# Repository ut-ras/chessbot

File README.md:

# ChessBot: Automated Chessboard

## Overview

ChessBot is an innovative project developed by the IEEE RAS - Demobots team. It is a CNC-inspired automated chessboard designed to enhance the experience of playing chess. Using an actuated electromagnet gantry system, ChessBot can move magnetized chess pieces across the board autonomously, allowing for a seamless game between two players or against a computer-controlled opponent. The project aims to merge the ancient game of chess with modern technology, providing a unique and interactive experience.

## Features

- **Automated Piece Movement**: Moves chess pieces using an electromagnet on a step-driven gantry system, controlled under the board.

- **Magnetized Chess Pieces**: Each piece is magnetized for precise and secure movement. Piece movements are detected via 3D magnetic sensors underneath each square.

- **Player vs. Computer Mode**: Play against an AI with adjustable difficulty settings.

- **Two-Player Online Mode**: Enjoy an enhanced tele-chess experience with automated piece movements that reflect your partner's movements from across the internet using Lichess

## Installation & Setup (WIP)

Make sure you have Python 3.6 or higher installed on your system. You can download it from the [official Python website](https://www.python.org/downloads/).

If on Windows use WSL for now, as the code is not tested on Windows.

1. Clone the repository to your local machine:

```bash
git clone https://github.com/ut-ras/chessbot.git 
```

2. Install the required Python packages:

```bash
cd chessbot
pip install -r requirements.txt
```
3. install stockfish and note what path it is installed to, you will need this for the python script. On Ubuntu or WSL you can do this with the following commands:

```bash
sudo apt-get install stockfish && which stockfish
```
The output of the `which stockfish` command will be the path to the stockfish binary. Copy that path, you will need this for the python script.

4. In the `python/bitboard_with_stockfish.py` file, change the `stockfish_path` variable to the path of the stockfish binary you found in the previous step.

5. Run the Python script:

```bash
python python/bitboard_with_stockfish.py
```

## Software

### Communication Structure

---
### Python Files
- [python/bitboard_with_stockfish.py](python/bitboard_with_stockfish.py) - This is the main file that runs the chess engine. It uses the python-chess library to interface with the Stockfish chess engine. The bitboard implementation is a custom implementation that uses 64-bit integers to represent the chessboard. Makes calls to functions in [python/display_output.py](python/display_output.py), animates the board for a 128x64 display, currently only makes the bitmap.

  - Bitboards are 64bit integer representations of the entire chessboard. 8x8 squares = 64 squares, so a digital for each individual square, that digit is 1 when a piece is on the corresponding square and 0 when a piece is absent from the square.
  - So far we arent using any "standard" bitboard implementations, as our situation is a tad unique. Most chess engines that utilize 12 bitboards, one for each piece type, ( [pawn + knight + bishop + rook + queen + king] * 2 teams = 12 piece types).
  - Here is a diagram of how each space on the chessboard is indexed in the bitboard, the number at each square is the digital that is either high or low depending on if a piece is there or not. For example, square `a4` is position `32`

     ``` 
       8 |  0  1  2  3  4  5  6  7
       7 |  8  9 10 11 12 13 14 15
       6 | 16 17 18 19 20 21 22 23
       5 | 24 25 26 27 28 29 30 31
       4 | 32 33 34 35 36 37 38 39
       3 | 40 41 42 43 44 45 46 47
       2 | 48 49 50 51 52 53 54 55
       1 | 56 57 58 59 60 61 62 63
          -------------------------
          a  b  c  d  e  f  g  h
      ```

## TODO
 - Assemble and test chessboard PCB's - each is an individual rank of the board that connect together.
-  Fill this section in with what we have left to do lol

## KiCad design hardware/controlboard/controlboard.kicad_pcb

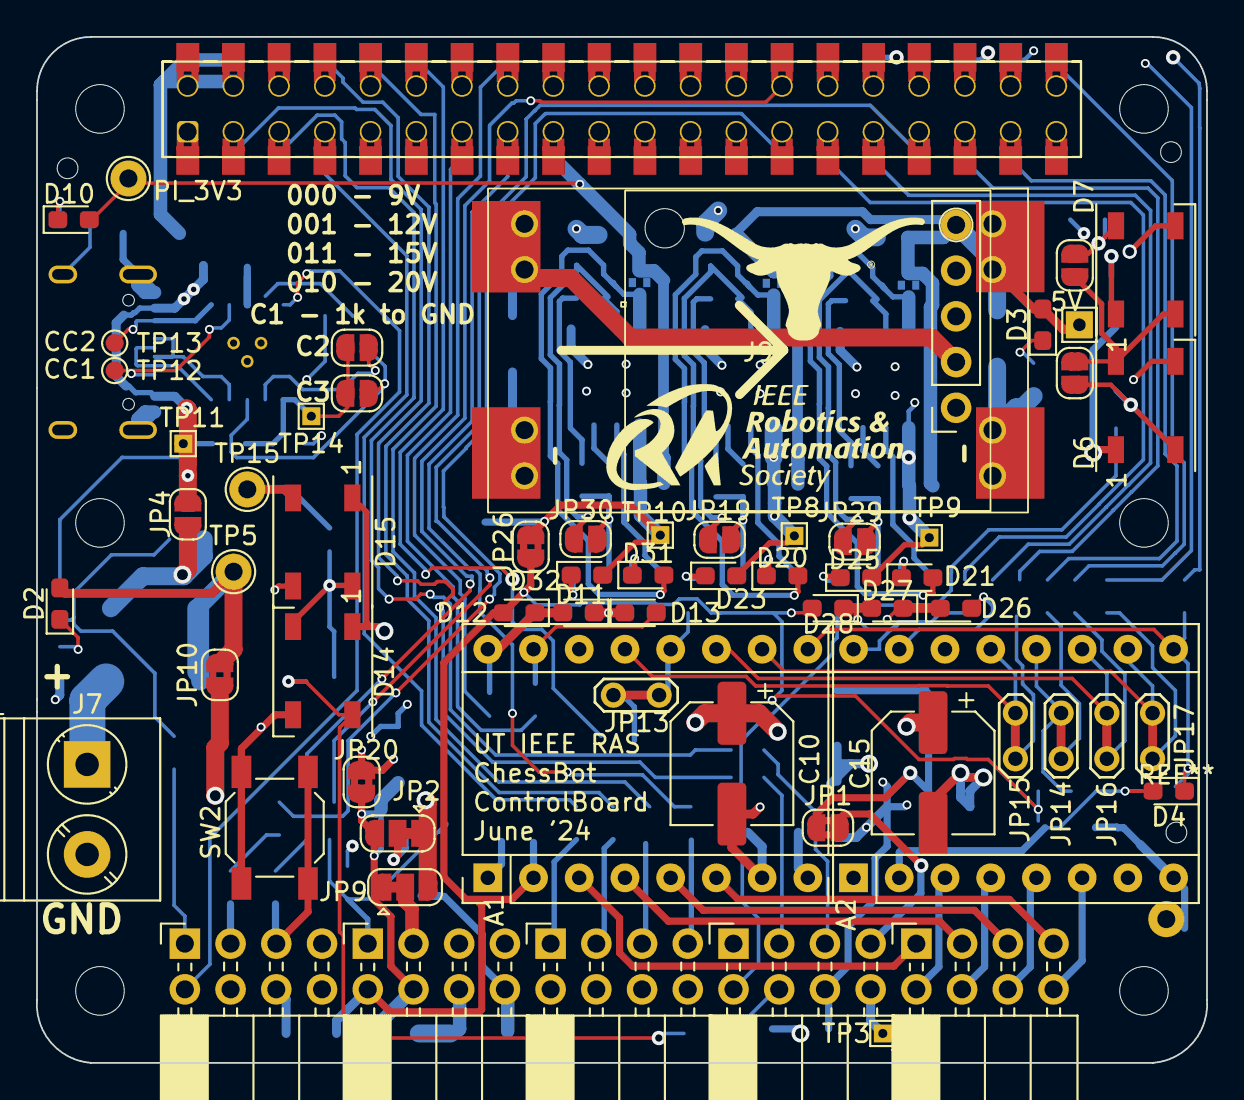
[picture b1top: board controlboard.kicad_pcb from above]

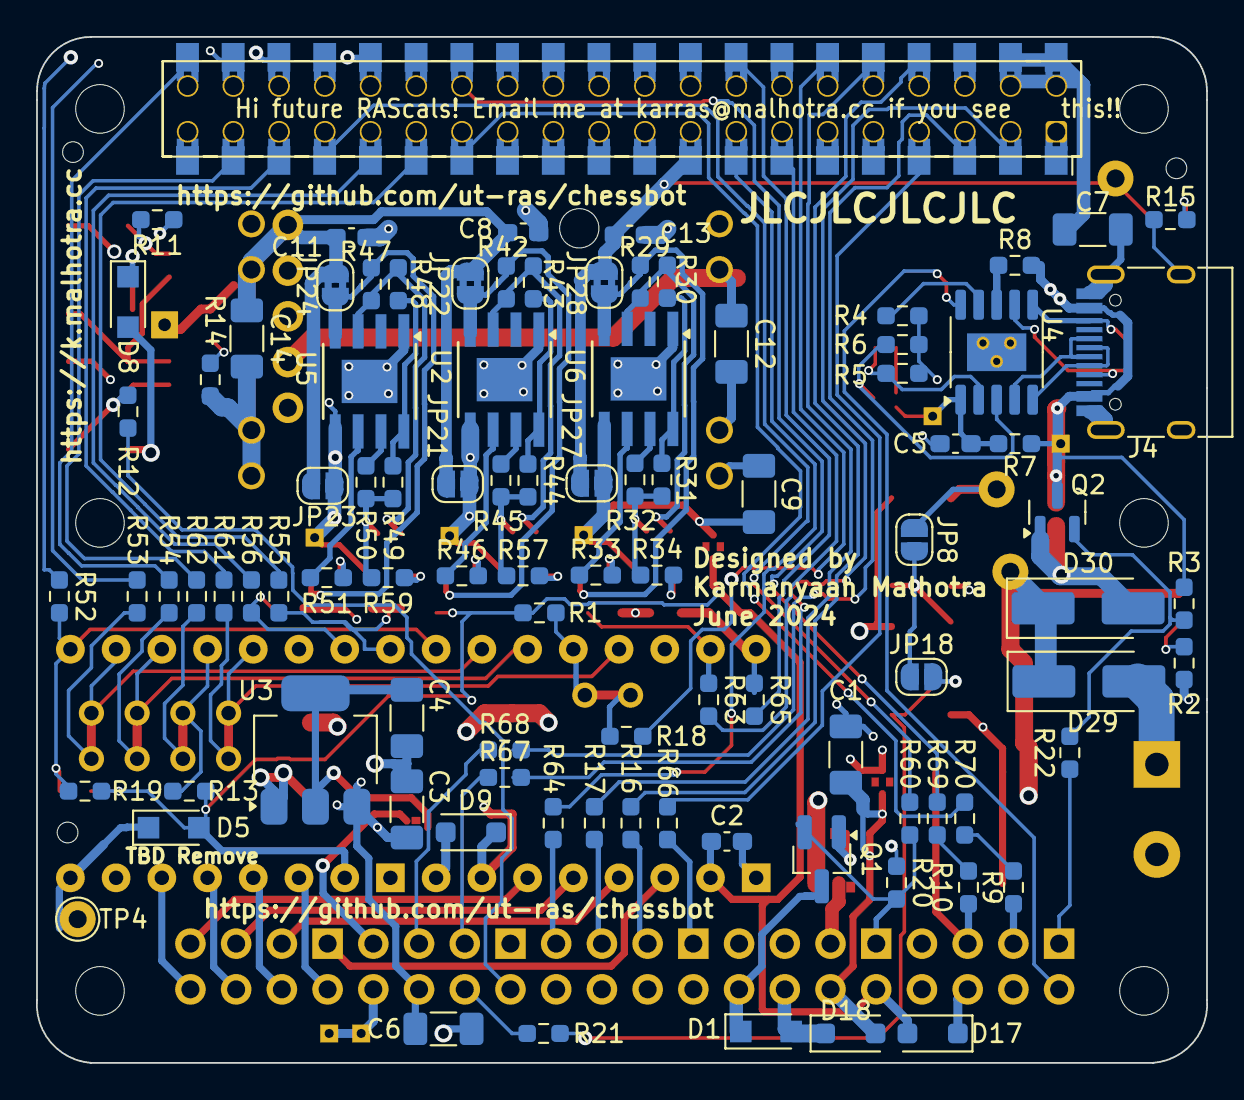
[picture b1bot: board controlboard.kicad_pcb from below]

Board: 4 copper layers, 65.0 x 57.0 mm, 166 parts (95 on the bottom side), 118 nets.

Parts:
A1: Pololu_Breakout_MP6500; Pololu_Breakout-16_15.2x20.3mm
A2: SilentStepStick TMC5160T; Pololu_Breakout-16_15.2x20.3mm
C1, C3, C4, C6, C7, C9, C12, C14: 22uF; C_1206_3216Metric_Pad1.33x1.80mm_HandSolder
C2, C8, C11, C13: 100n; C_0603_1608Metric_Pad1.08x0.95mm_HandSolder
C5: 1u; C_0603_1608Metric_Pad1.08x0.95mm_HandSolder
C10, C15: 100u; CP_Elec_6.3x5.4
D1, D5, D8: SM4007PL; Nexperia_CFP3_SOD-123W
D2, D3, D4, D10: Y; LED_0603_1608Metric_Pad1.05x0.95mm_HandSolder
D6, D7, D14, D15: WS2812B; LED_WS2812B_PLCC4_5.0x5.0mm_P3.2mm
D9: 20V+ D_TVS; D_SOD-123F
D11, D13, D23, D25, D26, D27, D32: G; LED_0603_1608Metric_Pad1.05x0.95mm_HandSolder
D12, D20, D21, D28, D31: R; LED_0603_1608Metric_Pad1.05x0.95mm_HandSolder
D17: 3V3V+ D_TVS; D_SOD-123F
D18: 6V+ D_TVS; D_SOD-123F
D29, D30: SS54; D_SMA_Handsoldering
J1, J3, J6: Conn_02x04_Counter_Clockwise; PinSocket_2x04_P2.54mm_Horizontal
J2: Conn_02x04_Row_Letter_Last; PinSocket_2x04_P2.54mm_Horizontal
J4: TYPE-C-31-M-12; USB_C_Receptacle_HRO_TYPE-C-31-M-12
J5: Conn_02x04_Row_Letter_First; PinSocket_2x04_P2.54mm_Horizontal
J7: Screw_Terminal_01x02; TerminalBlock_Phoenix_PT-1,5-2-5.0-H_1x02_P5.00mm_Horizontal
J9: mini560 voltage regulator; mini560
J11: Pololu Voltage Regulator; reg15d
J27: GPIO; Samtec_HLE-120-02-xxx-DV-BE-A_2x20_P2.54mm_Horizontal
JP1, JP10, JP20, JP22, JP24, JP26, JP28: SolderJumper_2_Bridged; SolderJumper-2_P1.3mm_Bridged2Bar_RoundedPad1.0x1.5mm
JP2, JP9: SolderJumper_3_Bridged12; SolderJumper-3_P1.3mm_Bridged12_RoundedPad1.0x1.5mm
JP4, JP8, JP11, JP12, JP18, JP19, JP29, JP30: SolderJumper_2_Open; SolderJumper-2_P1.3mm_Open_RoundedPad1.0x1.5mm
JP6, JP7: CFG3; SolderJumper-2_P1.3mm_Open_RoundedPad1.0x1.5mm
JP13, JP14, JP15, JP16, JP17: Jumper_2_Bridged; Bridged_TestPoint_2Pads_Pitch2.54mm_Drill0.8mm
JP21, JP23, JP27: Bypass; SolderJumper-2_P1.3mm_Open_RoundedPad1.0x1.5mm
MH1, MH2, MH3, MH3#2, MH4, MH4#2: MountingHole_2.7mm_M2.5
Q1: NMOS AO3400A; SOT-23_Handsoldering
Q2: PMOS AO3401A; SOT-23
R1, R3, R8, R13, R19, R20, R22, R43, R48: 10k; R_0603_1608Metric_Pad0.98x0.95mm_HandSolder
R2, R4, R5, R6, R7, R9, R10, R11, R12, R14, R15, R16, R17, R18, R21, R34, R52, R55, R56, R57, R59, R60, R62, R63, R64, R65, R66: 1k; R_0603_1608Metric_Pad0.98x0.95mm_HandSolder
R29: 82k; R_0603_1608Metric_Pad0.98x0.95mm_HandSolder
R30: 20k; R_0603_1608Metric_Pad0.98x0.95mm_HandSolder
R31, R44, R49: 47k; R_0603_1608Metric_Pad0.98x0.95mm_HandSolder
R32, R33, R46, R51: 3k; R_0603_1608Metric_Pad0.98x0.95mm_HandSolder
R42, R47: 150k; R_0603_1608Metric_Pad0.98x0.95mm_HandSolder
R45, R50: 470R; R_0603_1608Metric_Pad0.98x0.95mm_HandSolder
R53, R54, R61, R67, R68, R69, R70: 100; R_0603_1608Metric_Pad0.98x0.95mm_HandSolder
SW2: SW_Push TODO FP CHECK; SW_SPST_SKQG_WithStem
TP1, TP3, TP8, TP9, TP10, TP11, TP14: TestPoint; TestPoint_THTPad_1.0x1.0mm_Drill0.5mm
TP4, TP5, TP7, TP15: TestPoint; TestPoint_THTPad_D2.0mm_Drill1.0mm
TP6: TestPoint; TestPoint_THTPad_1.5x1.5mm_Drill0.7mm
TP12, TP13: TestPoint; TestPoint_Pad_D1.0mm
U2, U5, U6: TPS25963x; TI_SO-PowerPAD-8
U3: AMS1117-3.3; SOT-223-3_TabPin2
U4: CH224K; SSOP-10-1EP_3.9x4.9mm_P1mm_EP2.1x3.3mm

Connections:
/CH_5V: C3.1, C6.1, C15.1, D6.1 (VDD), D8.2 (A), D14.1 (VDD), D15.1 (VDD), D23.2 (A), J3.6, J6.4, JP20.2 (B), JP21.1 (A), TP8.1, U2.5 (OUT), U3.3 (VI)
/CH_SCL: J3.5, R68.1
/CH_SDA: J3.3, R67.1
/CNC/(CS/I1)1: A1.12 (I1), JP13.2 (B), R1.2
/CNC/(CS/I1)2: A2.12 (CS), JP14.2 (B), R13.2
/CNC/SCK/MS2: A1.11 (MS2), A2.11 (SCK), JP16.2 (B)
/CNC/SDI/MS1: A1.10 (MS1), A2.10 (SDI), JP17.2 (B)
/CNC/SDO/I2: A1.13 (I2), A2.13 (SDO), JP15.2 (B)
/CNC/SERVO_VIN: C1.1, D18.2 (A2), J5.4, JP2.1 (A), JP9.3 (B), JP20.1 (A)
/CNC/VIO: A1.2 (~FLT), A2.2 (VIO), C2.1, D4.2 (A), D5.2 (A), D12.2 (A), D17.2 (A2), D28.2 (A), J5.2, JP26.1 (A), R1.1, R13.1, R19.1
/CNC/VMOT: A1.8 (VMOT), A2.8 (VMOT), C10.1, D5.1 (K), D9.2 (A2), JP2.3 (B), JP9.1 (A), JP10.1 (A), TP4.1
/ChessBoard/3V3: C4.1, JP1.2 (B), U3.2 (VO)
/ChessBoard/LED_IN: D15.2 (DOUT), JP8.1 (A), TP15.1
/ChessBoard/LED_IN_REAL: D14.4 (DIN), JP18.2 (B), R21.2
/ChessBoard/LED_OUT: J3.2, R12.1
/DIR1: A1.16 (DIR), D11.2 (A), D12.1 (K), R65.1
/DIR2: A2.16 (DIR), D27.2 (A), D28.1 (K), R55.1
/ENBL: A1.9 (~ENABLE), A2.9 (~ENABLE), D4.1 (K), R19.2, R52.2
/ID_SCL: J6.5, R10.2, SW2.1
/ID_SDA: J6.3, R9.1
/LED_DATA: D7.4 (DIN), JP11.2 (B), R11.2
/LIM_SW1: J2.1, R66.1
/LIM_SW2: J2.3, R16.2
/LIM_SW3: J2.5, R17.2
/LIM_SW4: J2.7, R64.1
/MAG_PWM: J5.1, Q1.2 (G), R20.2, R60.1
/MOT_CS1: JP13.1 (A), R18.2
/MOT_CS2: JP14.1 (A), R62.1
/MOT_SCK: JP16.1 (A), R54.2
/MOT_SDI: JP17.1 (A), R53.2
/MOT_SDO: JP15.1 (A), R61.1
/PI_3V3: C13.1, D10.2 (A), J27.17, JP27.2 (B), JP28.2 (B), TP7.1
/PI_5V: C7.1, D25.2 (A), J27.2, J27.4, JP23.1 (A), TP9.1, U5.5 (OUT)
/Power/CH_VDD: C5.1, JP6.1 (A), JP7.1 (A), R7.1, TP14.1, U4.1 (VDD)
/Power/CNC_VIO: C9.1, D32.2 (A), JP26.2 (B), JP27.1 (A), TP10.1, U6.5 (OUT)
/Power/PWR_SW_A: J6.2, U4.10 (PG)
/Power/PWR_SW_B: J6.1, R22.1
/Power/UNLIM_5V: C8.1, C11.1, C14.1, D3.2 (A), J9.1, J11.5, JP21.2 (B), JP22.2 (B), JP23.2 (B), JP24.2 (B), TP6.1
/Power/UNLIM_VIN: C12.1, D2.2 (A), D29.1 (K), D30.1 (K), J6.8, J9.3, J11.2, JP10.2 (B), TP5.1
/Power/VBUS: J4.A4 (VBUS), J4.A9 (VBUS), J4.B4 (VBUS), J4.B9 (VBUS), JP4.1 (A), Q2.3 (S), R3.1, R7.2, R8.2, TP11.1
/STEP1: A1.15 (STEP), D13.2 (A), R63.1
/STEP2: A2.15 (STEP), D26.2 (A), R56.1
GND: A1.1 (GND), A1.7 (GND), A2.1 (GND), A2.7 (GND), C1.2, C2.2, C3.2, C4.2, C5.2, C6.2, C7.2, C8.2, C9.2, C10.2, C11.2, C12.2, C13.2, C14.2, C15.2, D1.2 (A), D6.3 (VSS), D7.3 (VSS), D9.1 (A1), D11.1 (K), D13.1 (K), D14.3 (VSS), D15.3 (VSS), D17.1 (A1), D18.1 (A1), D26.1 (K), D27.1 (K), J2.2, J2.4, J2.6, J2.8, J3.1, J4.A1 (GND), J4.A12 (GND), J4.B1 (GND), J4.B12 (GND), J4.S1 (SHIELD), J5.5, J5.6, J5.7, J6.6, J6.7, J7.2, J9.2, J9.4, J11.3, J11.4, J27.6, J27.9, J27.14, J27.20, J27.25, J27.30, J27.34, J27.39, JP19.1 (A), JP29.1 (A), JP30.1 (A), R2.1, R4.1, R5.1, R6.1, R14.1, R15.1, R20.1, R31.2, R32.2, R34.1, R44.2, R45.2, R49.2, R50.2, R57.1, R59.1, SW2.2, U2.1 (GND), U2.9 (GND), U3.1 (GND), U4.11 (GND), U5.1 (GND), U5.9 (GND), U6.1 (GND), U6.9 (GND)
unnamed: A1.4 (1A), J1.3
unnamed: A1.3 (1B), J1.1
unnamed: A1.5 (2A), J1.5
unnamed: A1.6 (2B), J1.7
unnamed: A2.4 (1A), J1.4
unnamed: A2.3 (1B), J1.2
unnamed: A2.5 (2A), J1.6
unnamed: A2.6 (2B), J1.8
unnamed: D1.1 (K), J5.8, Q1.3 (S)
unnamed: D2.1 (K), R2.2
unnamed: D3.1 (K), R14.2
unnamed: D6.4 (DIN), D7.2 (DOUT), JP11.1 (A), JP12.2 (B)
unnamed: D6.2 (DOUT), JP12.1 (A), R12.2
unnamed: D7.1 (VDD), D8.1 (K)
unnamed: D10.1 (K), R15.2
unnamed: D14.2 (DOUT), D15.4 (DIN), JP8.2 (B), JP18.1 (A)
unnamed: D20.2 (A), JP22.1 (A), R42.1, U2.4 (IN)
unnamed: D20.1 (K), R46.2
unnamed: D21.2 (A), JP24.1 (A), R47.1, U5.4 (IN)
unnamed: D21.1 (K), R51.2
unnamed: D23.1 (K), R57.2
unnamed: D25.1 (K), R59.2
unnamed: D29.2 (A), J7.1
unnamed: D30.2 (A), JP4.2 (B), Q2.1 (D)
unnamed: D31.2 (A), JP28.1 (A), R29.1, U6.4 (IN)
unnamed: D31.1 (K), R33.2
unnamed: D32.1 (K), R34.2
unnamed: J3.4, R21.1
unnamed: J3.7, JP1.1 (A)
unnamed: J3.8, TP1.1, TP3.1
unnamed: J4.A5 (CC1), TP12.1, U4.7 (CC1)
unnamed: J4.B5 (CC2), TP13.1, U4.6 (CC2)
unnamed: J5.3, JP2.2 (C)
unnamed: J27.3, R67.2
unnamed: J27.5, R68.2
unnamed: J27.7, R66.2
unnamed: J27.8, R16.1
unnamed: J27.10, R17.1
unnamed: J27.12, R18.1
unnamed: J27.13, R63.2
unnamed: J27.15, R64.2
unnamed: J27.16, R65.2
unnamed: J27.27, R70.2
unnamed: J27.28, R69.1
unnamed: J27.29, R55.2
unnamed: J27.31, R56.2
unnamed: J27.32, R11.1
unnamed: J27.33, R60.2
unnamed: J27.35, R61.2
unnamed: J27.36, R52.1
unnamed: J27.37, R62.2
unnamed: J27.38, R53.1
unnamed: J27.40, R54.1
unnamed: JP6.2 (B), R5.2, U4.2 (CFG2)
unnamed: JP7.2 (B), R6.2, U4.3 (CFG3)
unnamed: JP9.2 (C), Q1.1 (D)
unnamed: JP19.2 (B), R42.2, R43.1, U2.3 (EN/UVLO)
unnamed: JP29.2 (B), R47.2, R48.1, U5.3 (EN/UVLO)
unnamed: JP30.2 (B), R29.2, R30.1, U6.3 (EN/UVLO)
unnamed: Q2.2 (G), R3.2, R22.2
unnamed: R10.1, R69.2
unnamed: R9.2, R70.1
unnamed: R45.1, U2.7 (ILim)
unnamed: R43.2, R44.1, U2.8 (OVLO)
unnamed: R46.1, U2.6 (~FLT)
unnamed: R4.2, U4.9 (CFG1)
unnamed: J4.A7 (D-), J4.B7 (D-), U4.5 (DM)
unnamed: J4.A6 (D+), J4.B6 (D+), U4.4 (DP)
unnamed: R8.1, U4.8 (VBUS)
unnamed: R50.1, U5.7 (ILim)
unnamed: R48.2, R49.1, U5.8 (OVLO)
unnamed: R51.1, U5.6 (~FLT)
unnamed: R32.1, U6.7 (ILim)
unnamed: R30.2, R31.1, U6.8 (OVLO)
unnamed: R33.1, U6.6 (~FLT)

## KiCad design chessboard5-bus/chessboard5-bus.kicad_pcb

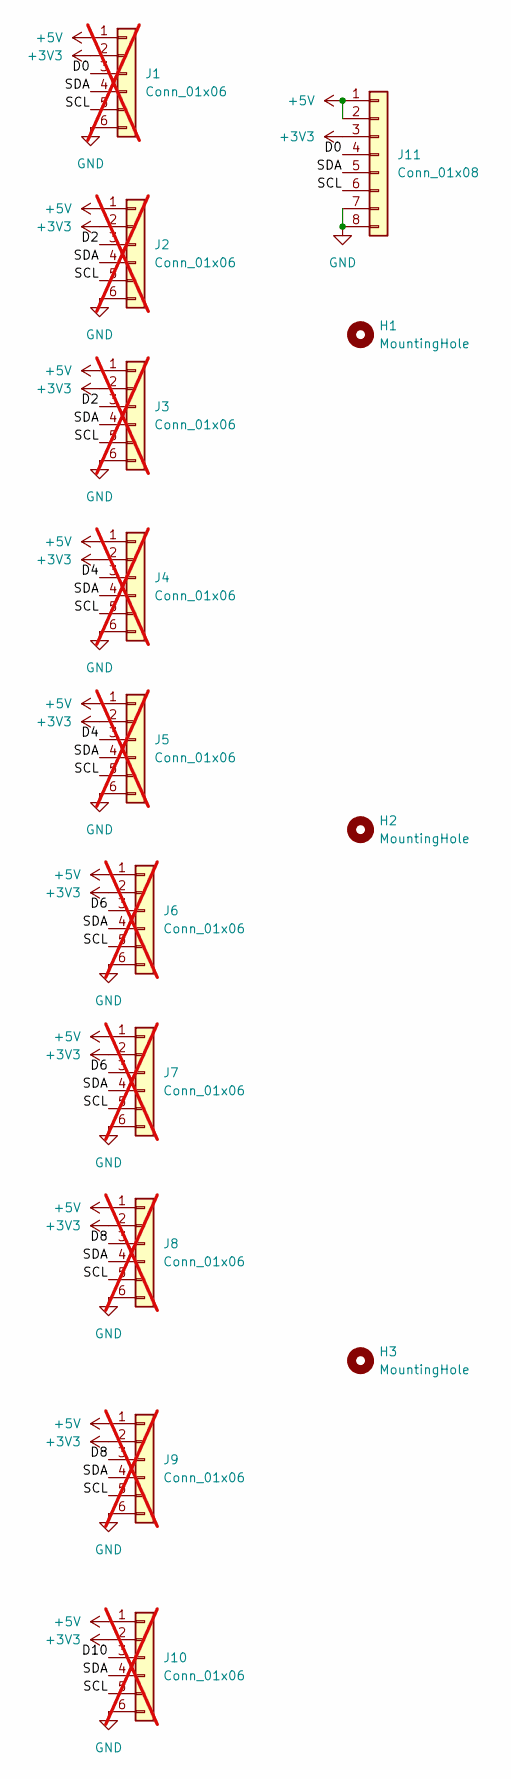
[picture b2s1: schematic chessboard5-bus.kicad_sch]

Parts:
H1, H2, H3: MountingHole; MountingHole_3.2mm_M3
J1, J2, J3, J4, J5, J6, J7, J8, J9, J10: Conn_01x06; PinHeader_2x03_P2.54mm_Vertical; not fitted
J11: Conn_01x08; JST_PH_S8B-PH-SM4-TB_1x08-1MP_P2.00mm_Horizontal

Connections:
+3V3: J1.2, J2.2, J3.2, J4.2, J5.2, J6.2, J7.2, J8.2, J9.2, J10.2, J11.3
+5V: J1.1, J2.1, J3.1, J4.1, J5.1, J6.1, J7.1, J8.1, J9.1, J10.1, J11.1, J11.2
/D0: J1.3, J11.4
/D2: J2.3, J3.3
/D4: J4.3, J5.3
/D6: J6.3, J7.3
/D8: J8.3, J9.3
/D10: J10.3
/SCL: J1.5, J2.5, J3.5, J4.5, J5.5, J6.5, J7.5, J8.5, J9.5, J10.5, J11.6
/SDA: J1.4, J2.4, J3.4, J4.4, J5.4, J6.4, J7.4, J8.4, J9.4, J10.4, J11.5
GND: J1.6, J2.6, J3.6, J4.6, J5.6, J6.6, J7.6, J8.6, J9.6, J10.6, J11.7, J11.8

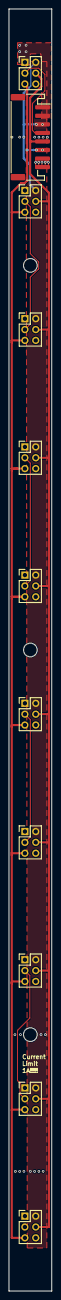
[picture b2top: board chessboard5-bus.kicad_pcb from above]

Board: 2 copper layers, 10.0 x 300.0 mm, 14 parts (0 on the bottom side), 10 nets.

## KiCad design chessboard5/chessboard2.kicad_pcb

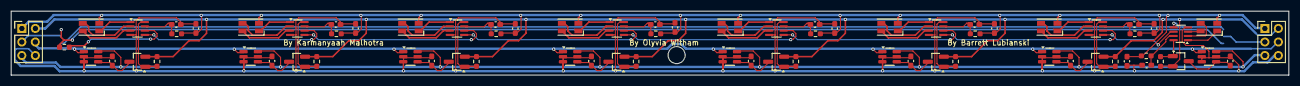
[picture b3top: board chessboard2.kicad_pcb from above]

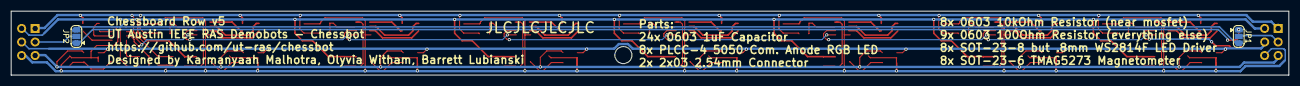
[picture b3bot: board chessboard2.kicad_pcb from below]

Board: 2 copper layers, 240.0 x 12.0 mm, 78 parts (2 on the bottom side), 65 nets.

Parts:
C1, C2, C3, C4, C5, C6, C7, C8, C9, C10, C11, C12, C13, C14, C15, C16, C17, C18, C19, C20, C21, C22, C23, C24: 1u; C_0603_1608Metric_Pad1.08x0.95mm_HandSolder
D9, D10, D11, D12, D13, D14, D15, D16: LED_RGAB; LED_RGB_Wuerth-PLCC4_3.2x2.8mm_150141M173100
H1: MountingHole; MountingHole_3.2mm_M3
J1, J2: Conn_01x06; PinHeader_2x03_P2.54mm_Vertical
JP1, JP2: SolderJumper_3_Open; SolderJumper-3_P1.3mm_Open_RoundedPad1.0x1.5mm
Q1, Q2, Q3, Q4, Q5, Q6, Q7, Q8: AO3401A; SOT-23_Handsoldering
R1, R3, R5, R7, R9, R11, R13, R15, R17: 100R; R_0603_1608Metric_Pad0.98x0.95mm_HandSolder
R2, R4, R6, R8, R10, R12, R14, R16: 10k; R_0603_1608Metric_Pad0.98x0.95mm_HandSolder
U1, U3, U5, U7, U9, U11, U13, U15: WS2814F; FSOP-8
U2, U4, U6, U8, U10, U12, U14, U16: TMAG5273; SOT-23-6_Handsoldering

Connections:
+3.3V: J1.2, J2.2, Q1.2 (S), Q2.2 (S), Q3.2 (S), Q4.2 (S), Q5.2 (S), Q6.2 (S), Q7.2 (S), Q8.2 (S), R2.2, R4.2, R6.2, R8.2, R10.2, R12.2, R14.2, R16.2
+5V: C1.1, C4.1, C7.1, C10.1, C13.1, C16.1, C19.1, C22.1, D9.4 (A), D10.4 (A), D11.4 (A), D12.4 (A), D13.4 (A), D14.4 (A), D15.4 (A), D16.4 (A), J1.1, J2.1, R1.1, R3.1, R5.1, R7.1, R9.1, R11.1, R13.1, R15.1
/Cell1/DOUT: U3.5 (DO), U5.6 (DIN)
/Cell2/DOUT: U5.5 (DO), U7.6 (DIN)
/Cell3/DOUT: U7.5 (DO), U9.6 (DIN)
/Cell4/DOUT: U9.5 (DO), U11.6 (DIN)
/Cell5/DOUT: U11.5 (DO), U13.6 (DIN)
/Cell6/DOUT: U13.5 (DO), U15.6 (DIN)
/Cell/DIN: R17.1, U1.6 (DIN)
/Cell/DOUT: U1.5 (DO), U3.6 (DIN)
/DIN_G: JP1.1 (A), JP2.1 (A), R17.2
/DOUT_G: JP1.3 (B), JP2.3 (B), U15.5 (DO)
GND: C1.2, C2.2, C3.2, C4.2, C5.2, C6.2, C7.2, C8.2, C9.2, C10.2, C11.2, C12.2, C13.2, C14.2, C15.2, C16.2, C17.2, C18.2, C19.2, C20.2, C21.2, C22.2, C23.2, C24.2, J1.6, J2.6, U1.4 (GND), U2.2 (GND), U2.3 (GND), U2.5 (GND), U3.4 (GND), U4.2 (GND), U4.3 (GND), U4.5 (GND), U5.4 (GND), U6.2 (GND), U6.3 (GND), U6.5 (GND), U7.4 (GND), U8.2 (GND), U8.3 (GND), U8.5 (GND), U9.4 (GND), U10.2 (GND), U10.3 (GND), U10.5 (GND), U11.4 (GND), U12.2 (GND), U12.3 (GND), U12.5 (GND), U13.4 (GND), U14.2 (GND), U14.3 (GND), U14.5 (GND), U15.4 (GND), U16.2 (GND), U16.3 (GND), U16.5 (GND)
unnamed: D9.2 (BK), U1.2 (OUTG)
unnamed: D9.1 (GK), U1.3 (OUTB)
unnamed: D9.3 (RK), U1.1 (OUTR)
unnamed: D10.2 (BK), U3.2 (OUTG)
unnamed: D10.1 (GK), U3.3 (OUTB)
unnamed: D10.3 (RK), U3.1 (OUTR)
unnamed: D11.2 (BK), U5.2 (OUTG)
unnamed: D11.1 (GK), U5.3 (OUTB)
unnamed: D11.3 (RK), U5.1 (OUTR)
unnamed: D12.2 (BK), U7.2 (OUTG)
unnamed: D12.1 (GK), U7.3 (OUTB)
unnamed: D12.3 (RK), U7.1 (OUTR)
unnamed: D13.2 (BK), U9.2 (OUTG)
unnamed: D13.1 (GK), U9.3 (OUTB)
unnamed: D13.3 (RK), U9.1 (OUTR)
unnamed: D14.2 (BK), U11.2 (OUTG)
unnamed: D14.1 (GK), U11.3 (OUTB)
unnamed: D14.3 (RK), U11.1 (OUTR)
unnamed: D15.2 (BK), U13.2 (OUTG)
unnamed: D15.1 (GK), U13.3 (OUTB)
unnamed: D15.3 (RK), U13.1 (OUTR)
unnamed: D16.2 (BK), U15.2 (OUTG)
unnamed: D16.1 (GK), U15.3 (OUTB)
unnamed: D16.3 (RK), U15.1 (OUTR)
unnamed: J1.3, JP2.2 (C)
unnamed: J2.3, JP1.2 (C)
unnamed: C3.1, Q1.3 (D), U2.4 (VDD)
unnamed: Q1.1 (G), R2.1, U1.8 (OUTW)
unnamed: C6.1, Q2.3 (D), U4.4 (VDD)
unnamed: Q2.1 (G), R4.1, U3.8 (OUTW)
unnamed: C9.1, Q3.3 (D), U6.4 (VDD)
unnamed: Q3.1 (G), R6.1, U5.8 (OUTW)
unnamed: C12.1, Q4.3 (D), U8.4 (VDD)
unnamed: Q4.1 (G), R8.1, U7.8 (OUTW)
unnamed: C15.1, Q5.3 (D), U10.4 (VDD)
unnamed: Q5.1 (G), R10.1, U9.8 (OUTW)
unnamed: C18.1, Q6.3 (D), U12.4 (VDD)
unnamed: Q6.1 (G), R12.1, U11.8 (OUTW)
unnamed: C21.1, Q7.3 (D), U14.4 (VDD)
unnamed: Q7.1 (G), R14.1, U13.8 (OUTW)
unnamed: C24.1, Q8.3 (D), U16.4 (VDD)
unnamed: Q8.1 (G), R16.1, U15.8 (OUTW)
unnamed: C2.1, R1.2, U1.7 (VDD)
unnamed: C5.1, R3.2, U3.7 (VDD)
unnamed: C8.1, R5.2, U5.7 (VDD)
unnamed: C11.1, R7.2, U7.7 (VDD)
unnamed: C14.1, R9.2, U9.7 (VDD)
unnamed: C17.1, R11.2, U11.7 (VDD)
unnamed: C20.1, R13.2, U13.7 (VDD)
unnamed: C23.1, R15.2, U15.7 (VDD)
SCL: J1.5, J2.5, U2.6 (SDA/ADDR), U4.6 (SDA/ADDR), U6.6 (SDA/ADDR), U8.6 (SDA/ADDR), U10.6 (SDA/ADDR), U12.6 (SDA/ADDR), U14.6 (SDA/ADDR), U16.6 (SDA/ADDR)
SDA: J1.4, J2.4, U2.1 (SCL/INT), U4.1 (SCL/INT), U6.1 (SCL/INT), U8.1 (SCL/INT), U10.1 (SCL/INT), U12.1 (SCL/INT), U14.1 (SCL/INT), U16.1 (SCL/INT)

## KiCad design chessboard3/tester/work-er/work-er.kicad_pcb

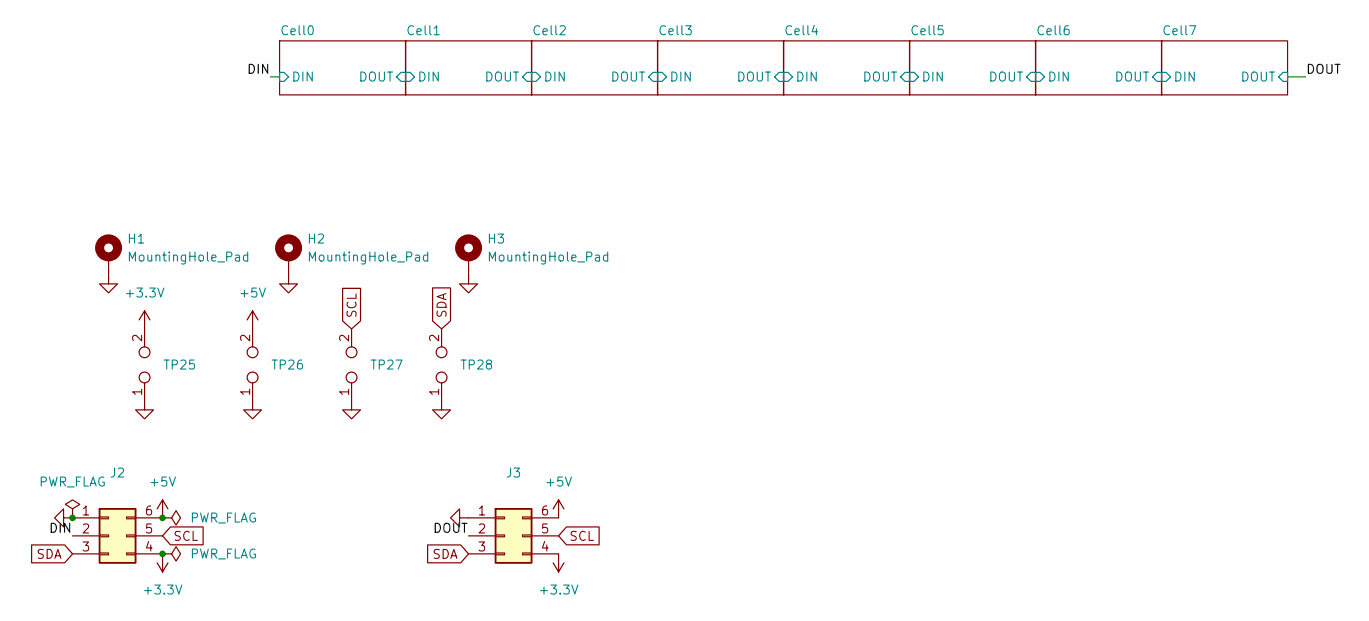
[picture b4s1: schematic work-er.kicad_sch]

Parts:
H1, H2, H3: MountingHole_Pad; MountingHole_2.2mm_M2_DIN965_Pad
J2, J3: Conn_02x03_Counter_Clockwise; PinHeader_2x03_P2.54mm_Vertical
TP25, TP26, TP27, TP28: TestPoint_2Pole; TestPoint_2Pads_Pitch2.54mm_Drill0.8mm

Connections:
+3.3V: J2.4, J3.4, TP25.2; also elsewhere on the board
+5V: J2.6, J3.6, TP26.2; also elsewhere on the board
/DIN: J2.2; also elsewhere on the board
/DOUT: J3.2; also elsewhere on the board
GND: H1.1, H2.1, H3.1, J2.1, J3.1, TP25.1, TP26.1, TP27.1, TP28.1; also elsewhere on the board
SCL: J2.5, J3.5, TP27.2; also elsewhere on the board
SDA: J2.3, J3.3, TP28.2; also elsewhere on the board

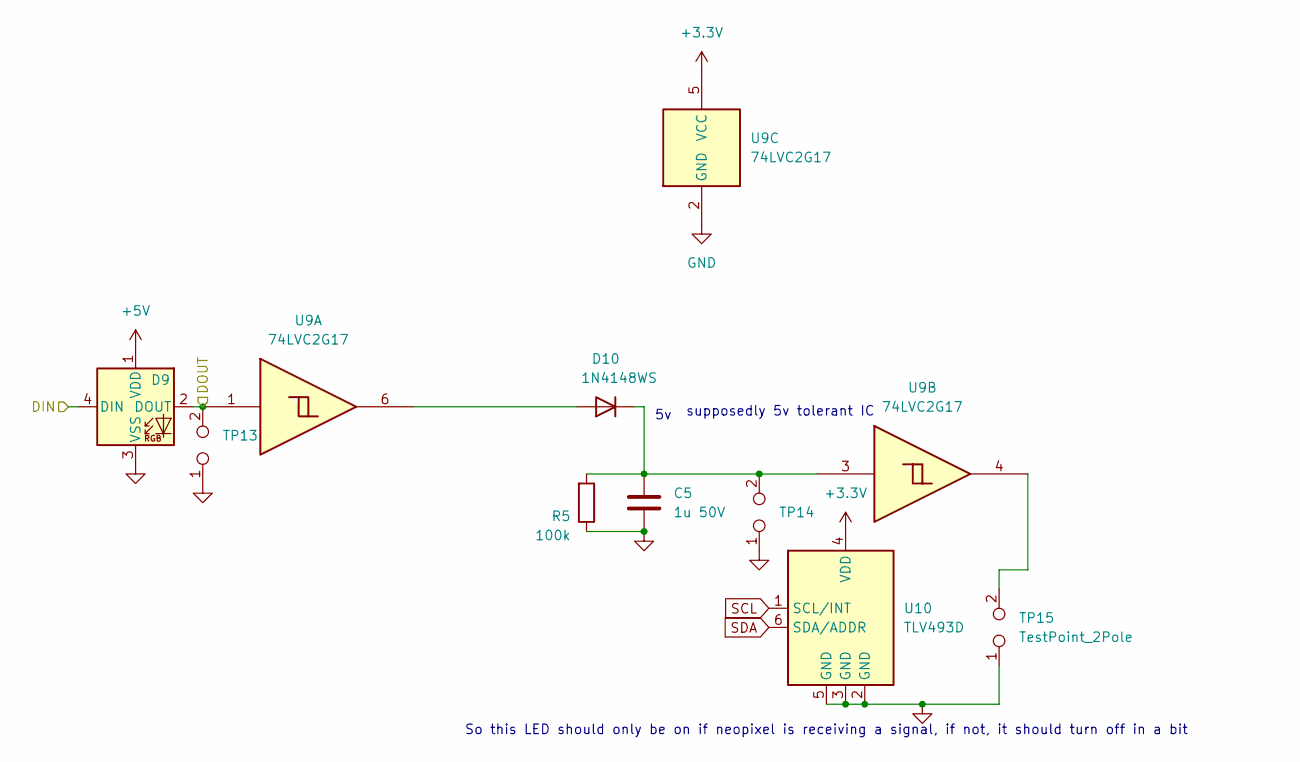
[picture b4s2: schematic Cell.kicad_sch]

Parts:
C5: 1u 50V; C_0603_1608Metric
D9: sk6812-mini-e; SK6812-MINI-E
D10: 1N4148WS; D_SOD-323_HandSoldering
R5: 100k; R_0603_1608Metric_Pad0.98x0.95mm_HandSolder
TP13, TP14, TP15: TestPoint_2Pole; TestPoint_2Pads_Pitch2.54mm_Drill0.8mm
U9: 74LVC2G17; SOT-363_SC-70-6_Handsoldering
U10: TLV493D; SOT-23-6_Handsoldering

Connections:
+3.3V: U9.5 (VCC), U10.4 (VDD); also elsewhere on the board
+5V: D9.1 (VDD); also elsewhere on the board
/Cell3/DOUT: D9.4 (DIN); also elsewhere on the board
/Cell4/DOUT: D9.2 (DOUT), TP13.2, U9.1; also elsewhere on the board
GND: C5.2, D9.3 (VSS), R5.1, TP13.1, TP14.1, TP15.1, U9.2 (GND), U10.2 (GND), U10.3 (GND), U10.5 (GND); also elsewhere on the board
unnamed: D10.2 (A), U9.6
unnamed: C5.1, D10.1 (K), R5.2, TP14.2, U9.3
unnamed: TP15.2, U9.4
SCL: U10.1 (SCL/INT); also elsewhere on the board
SDA: U10.6 (SDA/ADDR); also elsewhere on the board

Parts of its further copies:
C1, C2, C3, C4, C6, C7, C8: 1u 50V; C_0603_1608Metric
D1, D3, D5, D7, D11, D13, D15: sk6812-mini-e; SK6812-MINI-E
D2, D4, D6, D8, D12, D14, D16: 1N4148WS; D_SOD-323_HandSoldering
R1, R2, R3, R4, R6, R7, R8: 100k; R_0603_1608Metric_Pad0.98x0.95mm_HandSolder
TP1, TP2, TP3, TP4, TP5, TP6, TP7, TP8, TP9, TP10, TP11, TP12, TP16, TP17, TP18, TP19, TP20, TP21, TP22, TP23, TP24: TestPoint_2Pole; TestPoint_2Pads_Pitch2.54mm_Drill0.8mm
U1, U3, U5, U7, U11, U13, U15: 74LVC2G17; SOT-363_SC-70-6_Handsoldering
U2, U4, U6, U8, U12, U14, U16: TLV493D; SOT-23-6_Handsoldering

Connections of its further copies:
+3.3V: U1.5 (VCC), U2.4 (VDD), U3.5 (VCC), U4.4 (VDD), U5.5 (VCC), U6.4 (VDD), U7.5 (VCC), U8.4 (VDD), U11.5 (VCC), U12.4 (VDD), U13.5 (VCC), U14.4 (VDD), U15.5 (VCC), U16.4 (VDD); also elsewhere on the board
+5V: D1.1 (VDD), D3.1 (VDD), D5.1 (VDD), D7.1 (VDD), D11.1 (VDD), D13.1 (VDD), D15.1 (VDD); also elsewhere on the board
/Cell0/DOUT: D1.2 (DOUT), D3.4 (DIN), TP1.2, U1.1
/Cell1/DOUT: D3.2 (DOUT), D5.4 (DIN), TP4.2, U3.1
/Cell2/DOUT: D5.2 (DOUT), D7.4 (DIN), TP7.2, U5.1
/Cell3/DOUT: D7.2 (DOUT), TP10.2, U7.1; also elsewhere on the board
/Cell4/DOUT: D11.4 (DIN); also elsewhere on the board
/Cell5/DOUT: D11.2 (DOUT), D13.4 (DIN), TP16.2, U11.1
/Cell6/DOUT: D13.2 (DOUT), D15.4 (DIN), TP19.2, U13.1
/DIN: D1.4 (DIN); also elsewhere on the board
/DOUT: D15.2 (DOUT), TP22.2, U15.1; also elsewhere on the board
GND: C1.2, C2.2, C3.2, C4.2, C6.2, C7.2, C8.2, D1.3 (VSS), D3.3 (VSS), D5.3 (VSS), D7.3 (VSS), D11.3 (VSS), D13.3 (VSS), D15.3 (VSS), R1.1, R2.1, R3.1, R4.1, R6.1, R7.1, R8.1, TP1.1, TP2.1, TP3.1, TP4.1, TP5.1, TP6.1, TP7.1, TP8.1, TP9.1, TP10.1, TP11.1, TP12.1, TP16.1, TP17.1, TP18.1, TP19.1, TP20.1, TP21.1, TP22.1, TP23.1, TP24.1, U1.2 (GND), U2.2 (GND), U2.3 (GND), U2.5 (GND), U3.2 (GND), U4.2 (GND), U4.3 (GND), U4.5 (GND), U5.2 (GND), U6.2 (GND), U6.3 (GND), U6.5 (GND), U7.2 (GND), U8.2 (GND), U8.3 (GND), U8.5 (GND), U11.2 (GND), U12.2 (GND), U12.3 (GND), U12.5 (GND), U13.2 (GND), U14.2 (GND), U14.3 (GND), U14.5 (GND), U15.2 (GND), U16.2 (GND), U16.3 (GND), U16.5 (GND); also elsewhere on the board
unnamed: D2.2 (A), U1.6
unnamed: C1.1, D2.1 (K), R1.2, TP2.2, U1.3
unnamed: D4.2 (A), U3.6
unnamed: C2.1, D4.1 (K), R2.2, TP5.2, U3.3
unnamed: D6.2 (A), U5.6
unnamed: C3.1, D6.1 (K), R3.2, TP8.2, U5.3
unnamed: D8.2 (A), U7.6
unnamed: C4.1, D8.1 (K), R4.2, TP11.2, U7.3
unnamed: D12.2 (A), U11.6
unnamed: C6.1, D12.1 (K), R6.2, TP17.2, U11.3
unnamed: D14.2 (A), U13.6
unnamed: C7.1, D14.1 (K), R7.2, TP20.2, U13.3
unnamed: D16.2 (A), U15.6
unnamed: C8.1, D16.1 (K), R8.2, TP23.2, U15.3
unnamed: TP3.2, U1.4
unnamed: TP6.2, U3.4
unnamed: TP9.2, U5.4
unnamed: TP12.2, U7.4
unnamed: TP18.2, U11.4
unnamed: TP21.2, U13.4
unnamed: TP24.2, U15.4
SCL: U2.1 (SCL/INT), U4.1 (SCL/INT), U6.1 (SCL/INT), U8.1 (SCL/INT), U12.1 (SCL/INT), U14.1 (SCL/INT), U16.1 (SCL/INT); also elsewhere on the board
SDA: U2.6 (SDA/ADDR), U4.6 (SDA/ADDR), U6.6 (SDA/ADDR), U8.6 (SDA/ADDR), U12.6 (SDA/ADDR), U14.6 (SDA/ADDR), U16.6 (SDA/ADDR); also elsewhere on the board

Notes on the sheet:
supposedly 5v tolerant IC
So this LED should only be on if neopixel is receiving a signal, if not, it should turn off in a bit

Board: 2 copper layers, 81 parts (0 on the bottom side), 38 nets, no tracks yet.

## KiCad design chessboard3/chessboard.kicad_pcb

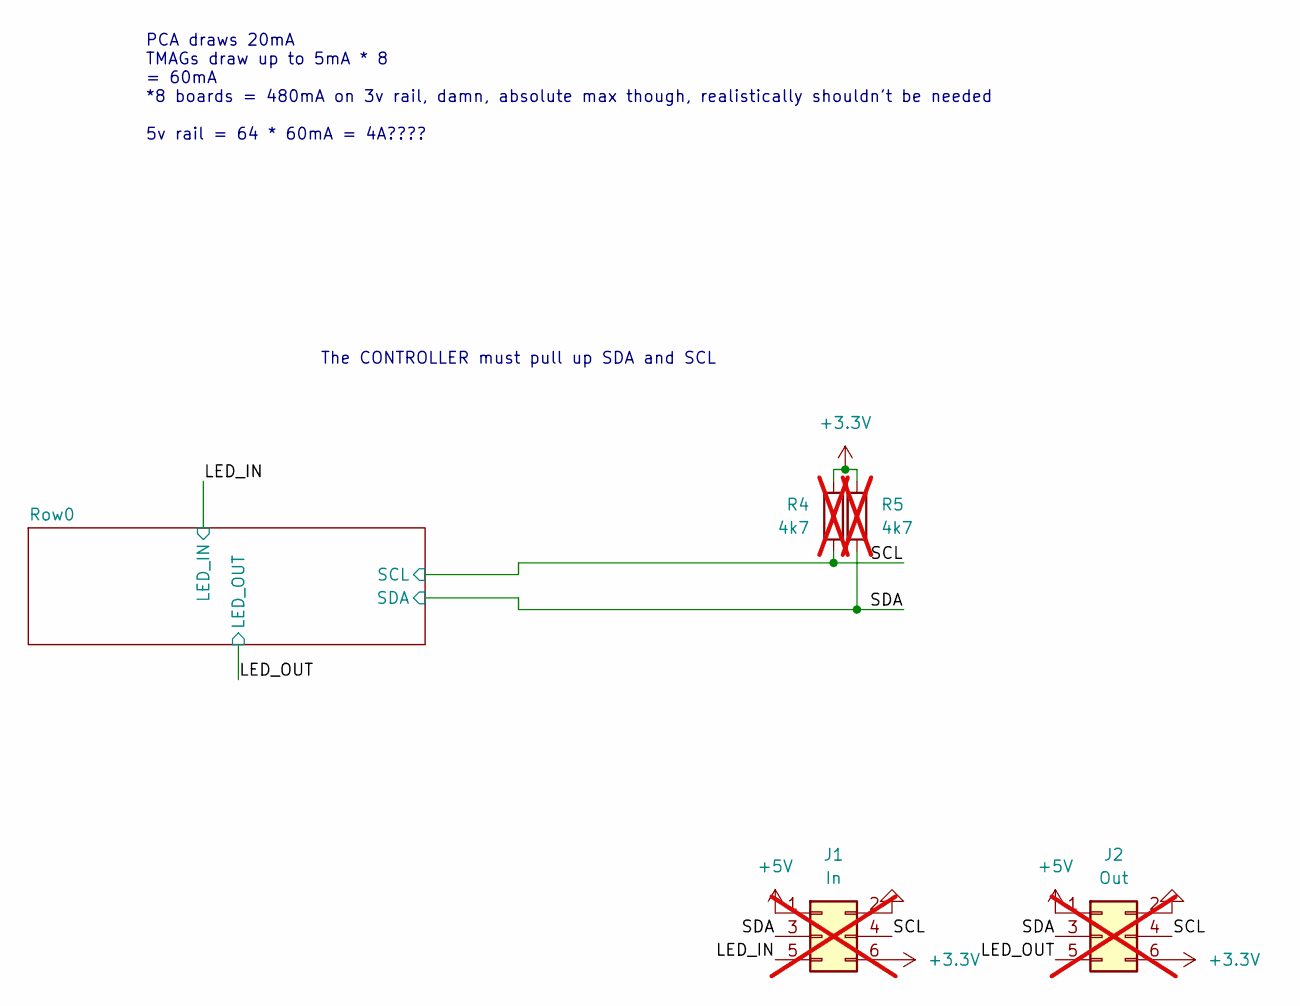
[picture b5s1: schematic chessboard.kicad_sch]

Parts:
J1: In; PinSocket_2x03_P2.54mm_Vertical; not fitted
J2: Out; PinSocket_2x03_P2.54mm_Vertical; not fitted
R4, R5: 4k7; R_0603_1608Metric; not fitted

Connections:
+3.3V: J1.6, J2.6, R4.1, R5.1; also elsewhere on the board
+5V: J1.1, J2.1; also elsewhere on the board
/LED_IN: J1.5; also elsewhere on the board
/LED_OUT: J2.5; also elsewhere on the board
/SCL: J1.4, J2.4, R4.2; also elsewhere on the board
/SDA: J1.3, J2.3, R5.2; also elsewhere on the board
GND: J1.2, J2.2; also elsewhere on the board

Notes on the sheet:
PCA draws 20mA TMAGs draw up to 5mA * 8 = 60mA *8 boards = 480mA on 3v rail, damn, absolute max though, realistically shouldn't be needed 5v rail = 64 * 60mA = 4A????
The CONTROLLER must pull up SDA and SCL

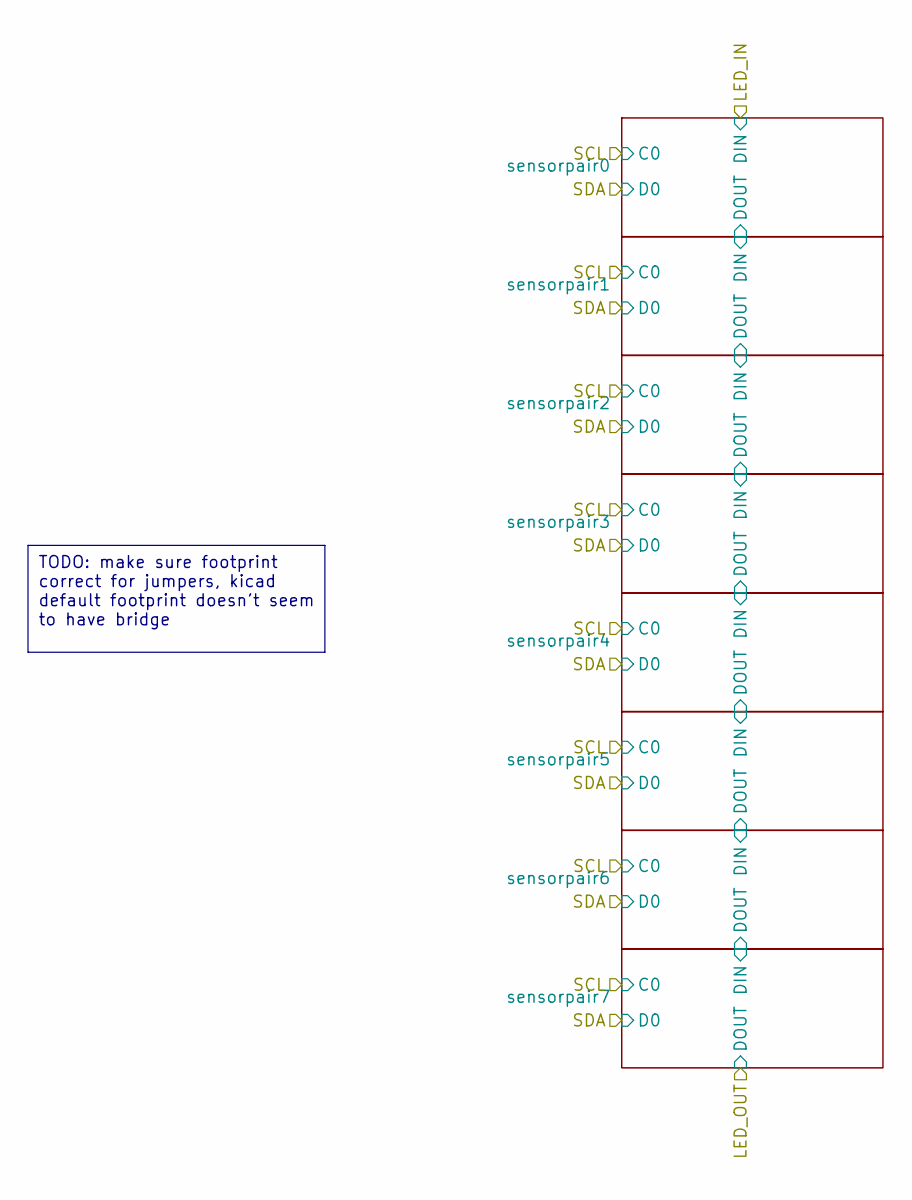
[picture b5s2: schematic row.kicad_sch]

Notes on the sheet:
TODO: make sure footprint correct for jumpers, kicad default footprint doesn't seem to have bridge
